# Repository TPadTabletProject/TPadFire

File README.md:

TPadFire
========

Original repo for the TPadFire project. This is the original TPad/Android device introduced in 2013.

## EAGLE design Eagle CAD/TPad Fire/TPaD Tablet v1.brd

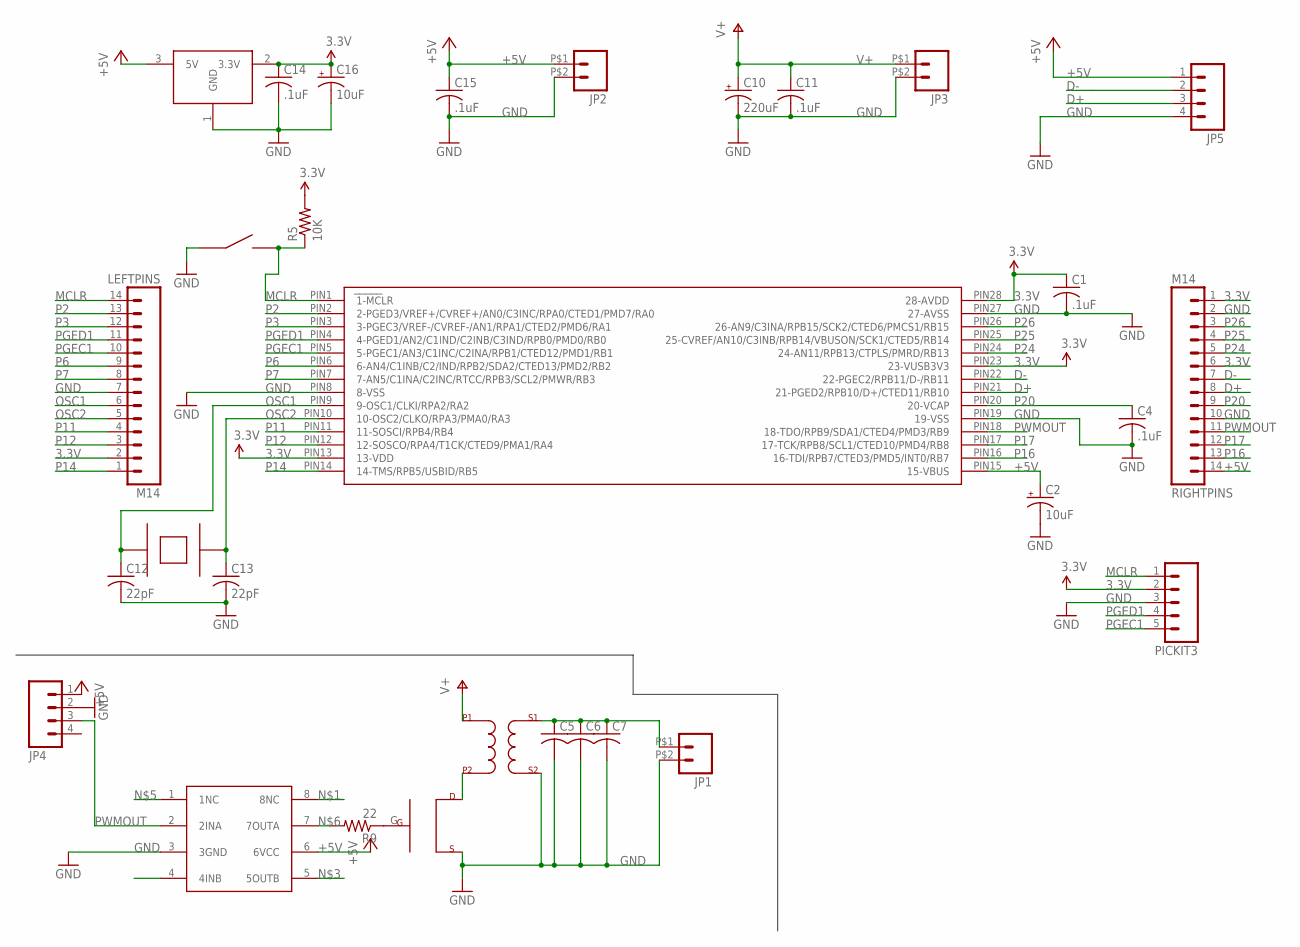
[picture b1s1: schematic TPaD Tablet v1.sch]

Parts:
C1, C4, C11, C14, C15: .1uF; C050-035X075
C2, C16: 10uF; E2-5
C5, C6, C7: C-US050-035X075; C050-035X075
C10: 220uF; TT2D6
C12, C13: 22pF; C025-024X044
JP1, JP2, JP3: M02PTH2; 1X02_BIG
JP4, JP5: M04PTH; 1X04
LEFTPINS: M14; 1X14
PICKIT3: M05PTH; 1X05
R5: 10K; 0207/10
R9: 22; 0207/10
RIGHTPINS: M14; 1X14
U$1: PIC32MX250F128B; DIP28-PIC32
U$3: GATEDRIVER; DIL-08
U$4: TRANSFORMER
U$5: TPAD_IRF520N; TPAD_TO220
U$6: LD33V; SOT223
U$7: OSCILLATOR; OSC
U$8: SWITCH; OSC

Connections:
3.3V: C1.1, C14.1, C16.+, LEFTPINS.2, PICKIT3.2, R5.2, RIGHTPINS.1, RIGHTPINS.6, U$1.PIN13 (13-VDD), U$1.PIN23 (23-VUSB3V3), U$1.PIN28 (28-AVDD), U$6.2 (3.3V)
+5V: C2.+, C15.1, JP2.P$1 (1), JP4.1, JP5.1, RIGHTPINS.14, U$1.PIN15 (15-VBUS), U$3.6 (6VCC), U$6.3 (5V)
D+: JP5.3, RIGHTPINS.8, U$1.PIN21 (21-PGED2/RPB10/D+/CTED11/RB10)
D-: JP5.2, RIGHTPINS.7, U$1.PIN22 (22-PGEC2/RPB11/D-/RB11)
GND: C1.2, C2.-, C4.2, C5.2, C6.2, C7.2, C10.-, C11.2, C12.2, C13.2, C14.2, C15.2, C16.-, JP1.P$2 (2), JP2.P$2 (2), JP3.P$2 (2), JP4.2, JP5.4, LEFTPINS.7, PICKIT3.3, RIGHTPINS.2, RIGHTPINS.10, U$1.PIN8 (8-VSS), U$1.PIN19 (19-VSS), U$1.PIN27 (27-AVSS), U$3.3 (3GND), U$4.S2, U$5.S, U$6.1 (GND), U$8.P$1
MCLR: LEFTPINS.14, PICKIT3.1, R5.1, U$1.PIN1 (1-MCLR), U$8.P$3
unnamed: R9.2, U$3.7 (7OUTA)
unnamed: R9.1, U$5.G
unnamed: U$4.P2, U$5.D
unnamed: C5.1, C6.1, C7.1, JP1.P$1 (1), U$4.S1
OSC1: C12.1, LEFTPINS.6, U$1.PIN9 (9-OSC1/CLKI/RPA2/RA2), U$7.P$3
OSC2: C13.1, LEFTPINS.5, U$1.PIN10 (10-OSC2/CLKO/RPA3/PMA0/RA3), U$7.P$1
P2: LEFTPINS.13, U$1.PIN2 (2-PGED3/VREF+/CVREF+/AN0/C3INC/RPA0/CTE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)
P3: LEFTPINS.12, U$1.PIN3 (3-PGEC3/VREF-/CVREF-/AN1/RPA1/CTED2/PMD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)
P6: LEFTPINS.9, U$1.PIN6 (6-AN4/C1INB/C2/IND/RPB2/SDA2/CTED13/PMD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)
P7: LEFTPINS.8, U$1.PIN7 (7-AN5/C1INA/C2INC/RTCC/RPB3/SCL2/PMWR/R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)
P11: LEFTPINS.4, U$1.PIN11 (11-SOSCI/RPB4/RB4)
P12: LEFTPINS.3, U$1.PIN12 (12-SOSCO/RPA4/T1CK/CTED9/PMA1/RA4)
P14: LEFTPINS.1, U$1.PIN14 (14-TMS/RPB5/USBID/RB5)
P16: RIGHTPINS.13, U$1.PIN16 (16-TDI/RPB7/CTED3/PMD5/INT0/RB7)
P17: RIGHTPINS.12, U$1.PIN17 (17-TCK/RPB8/SCL1/CTED10/PMD4/RB8)
P20: C4.1, RIGHTPINS.9, U$1.PIN20 (20-VCAP)
P24: RIGHTPINS.5, U$1.PIN24 (24-AN11/RPB13/CTPLS/PMRD/RB13)
P25: RIGHTPINS.4, U$1.PIN25 (25-CVREF/AN10/C3INB/RPB14/VBUSON/SCK1/C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)
P26: RIGHTPINS.3, U$1.PIN26 (26-AN9/C3INA/RPB15/SCK2/CTED6/PMCS1/RB15)
PGEC1: LEFTPINS.10, PICKIT3.5, U$1.PIN5 (5-PGEC1/AN3/C1INC/C2INA/RPB1/CTED12/PMD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)
PGED1: LEFTPINS.11, PICKIT3.4, U$1.PIN4 (4-PGED1/AN2/C1IND/C2INB/C3IND/RPB0/PMD0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)
PWMOUT: JP4.3, RIGHTPINS.11, U$1.PIN18 (18-TDO/RPB9/SDA1/CTED4/PMD3/RB9), U$3.2 (2INA)
V+: C10.+, C11.1, JP3.P$1 (1), U$4.P1

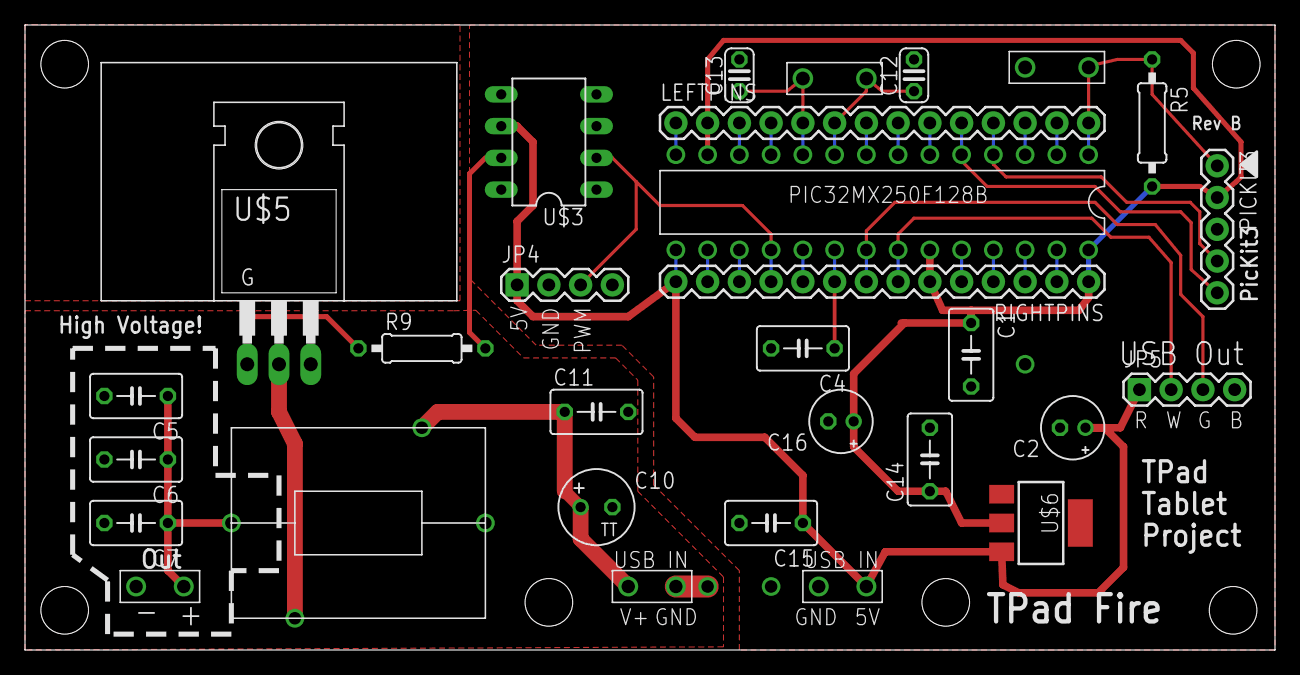
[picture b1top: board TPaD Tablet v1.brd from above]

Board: 2 copper layers, 100.0 x 50.0 mm, 30 parts (0 on the bottom side), 29 nets.

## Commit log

2014-10-15 Consolidating TPadFire files into a single repo

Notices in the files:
parts and their libraries:
SparkFun-Connectors: Licensing: CC v3.0 Share-Alike You are welcome to use this library for commercial purposes.
